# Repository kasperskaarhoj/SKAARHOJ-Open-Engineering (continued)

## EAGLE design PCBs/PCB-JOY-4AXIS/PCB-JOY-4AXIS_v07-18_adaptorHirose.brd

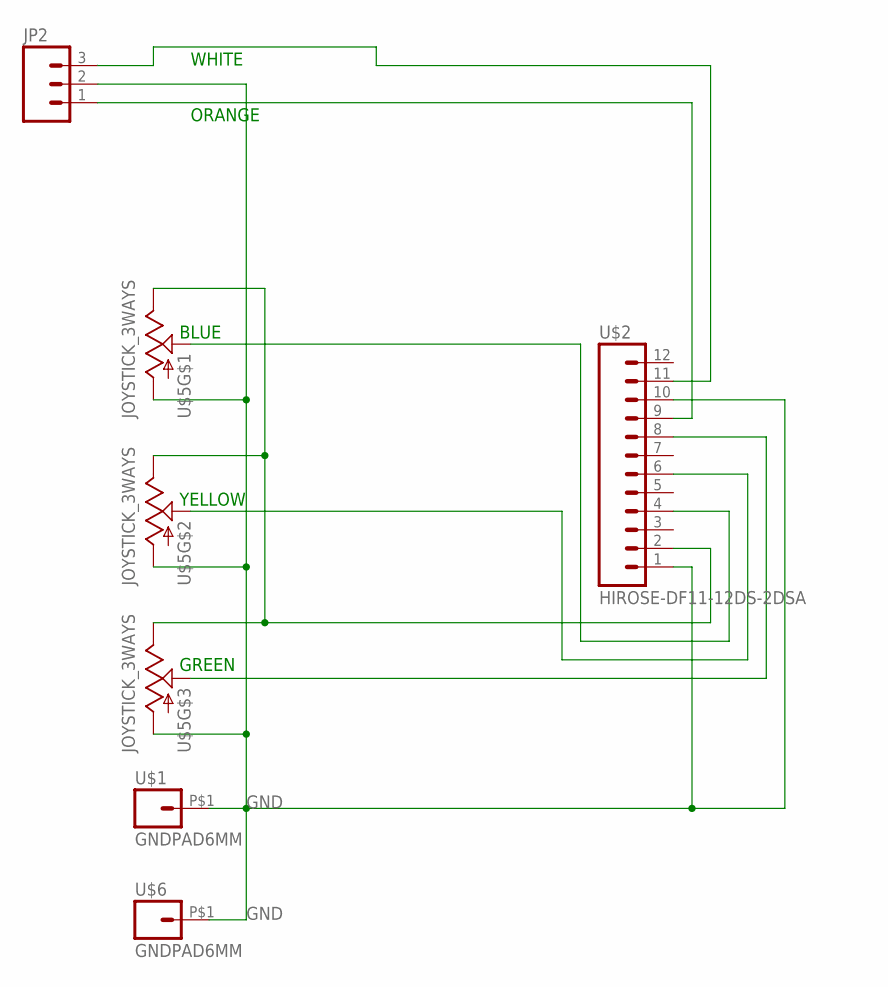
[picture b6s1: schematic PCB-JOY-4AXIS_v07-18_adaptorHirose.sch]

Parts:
JP2: M03PTH; 1X03
U$1, U$6: GNDPAD6MM; 3.2MMPAD6MM
U$2: HIROSE-DF11-12DS-2DSA; 2X6HIROSE_DF11-12DS-2DSA
U$5: JOYSTICK_3WAYS; JOYSTICK

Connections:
GND: JP2.2, U$1.P$1, U$2.1, U$2.10, U$5.LR_COM (A), U$5.ROT_COM (A), U$5.UD_COM (A), U$6.P$1
unnamed: U$2.2, U$5.LR_V (E), U$5.ROT_V (E), U$5.UD_V (E)
unnamed: U$2.4, U$5.LR_C (S)
unnamed: U$2.6, U$5.UD_C (S)
unnamed: U$2.8, U$5.ROT_C (S)
unnamed: JP2.1, U$2.9
unnamed: JP2.3, U$2.11

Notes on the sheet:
GREEN
ORANGE
WHITE
YELLOW
BLUE

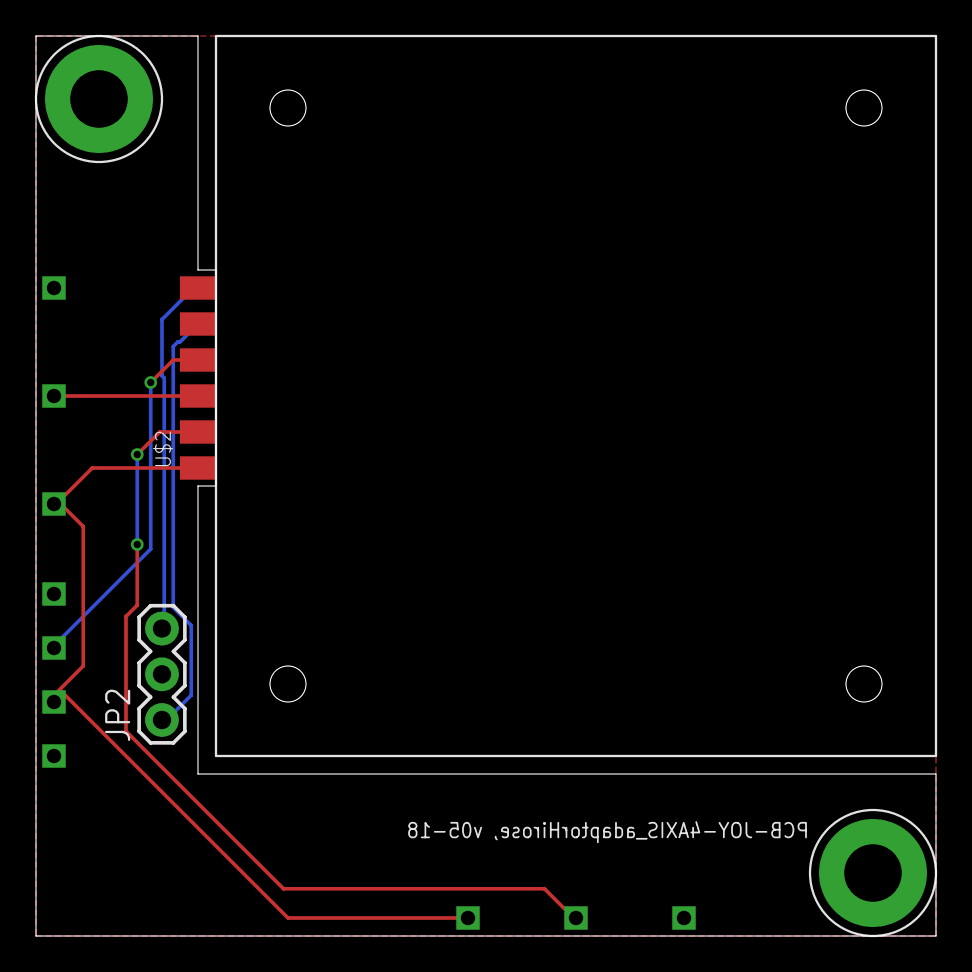
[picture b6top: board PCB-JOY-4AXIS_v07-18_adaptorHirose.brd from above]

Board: 2 copper layers, 50.0 x 50.0 mm, 5 parts (0 on the bottom side), 7 nets.

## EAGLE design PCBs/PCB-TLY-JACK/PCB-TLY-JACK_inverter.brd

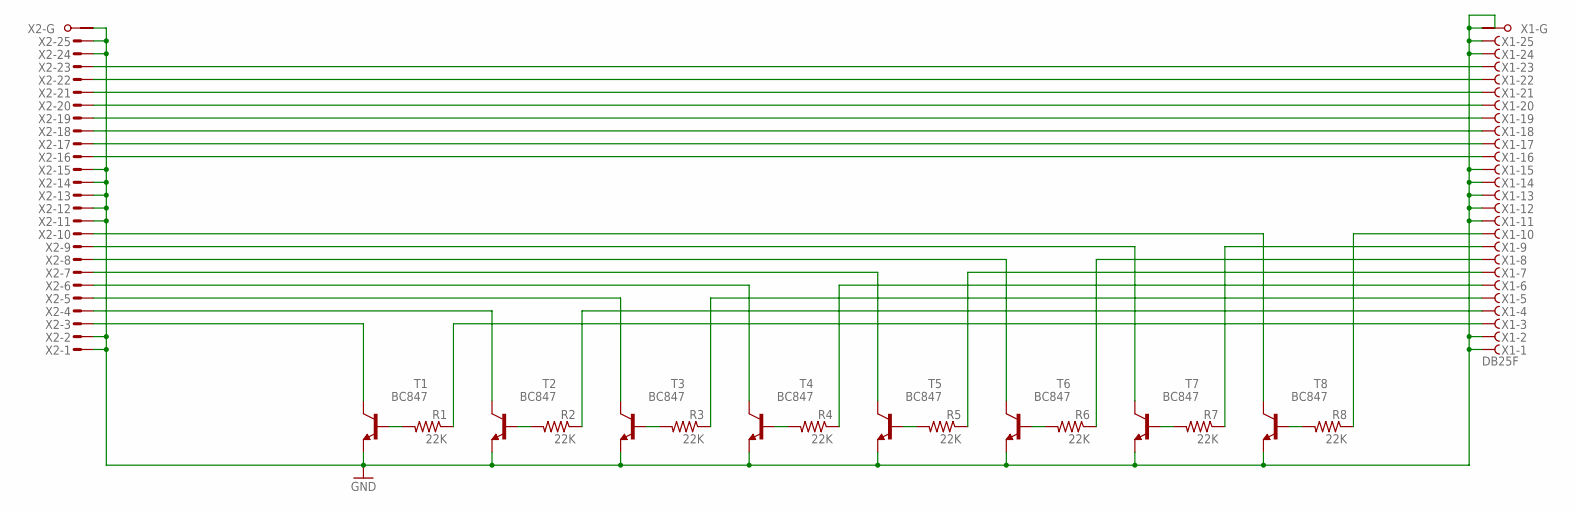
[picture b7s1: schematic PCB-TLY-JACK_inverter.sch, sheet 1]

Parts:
R1, R2, R3, R4, R5, R6, R7, R8: 22K; 0603-RES
T1, T2, T3, T4, T5, T6, T7, T8: BC847; SOT23
X1: DB25F; F25HP
X2: M25HPS; M25HP

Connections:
GND: T1.2 (E), T2.2 (E), T3.2 (E), T4.2 (E), T5.2 (E), T6.2 (E), T7.2 (E), T8.2 (E), X1.1 (F), X1.2 (F), X1.11 (F), X1.12 (F), X1.13 (F), X1.14 (F), X1.15 (F), X1.24 (F), X1.25 (F), X1.G1, X1.G2, X2.1 (M), X2.2 (M), X2.11 (M), X2.12 (M), X2.13 (M), X2.14 (M), X2.15 (M), X2.24 (M), X2.25 (M), X2.G1
unnamed: X1.23 (F), X2.23 (M)
unnamed: T8.3 (C), X2.10 (M)
unnamed: R1.2, T1.1 (B)
unnamed: T7.3 (C), X2.9 (M)
unnamed: X1.22 (F), X2.22 (M)
unnamed: T6.3 (C), X2.8 (M)
unnamed: T5.3 (C), X2.7 (M)
unnamed: T4.3 (C), X2.6 (M)
unnamed: X1.21 (F), X2.21 (M)
unnamed: T3.3 (C), X2.5 (M)
unnamed: T2.3 (C), X2.4 (M)
unnamed: R2.2, T2.1 (B)
unnamed: X1.20 (F), X2.20 (M)
unnamed: R3.2, T3.1 (B)
unnamed: R4.2, T4.1 (B)
unnamed: R5.2, T5.1 (B)
unnamed: X1.19 (F), X2.19 (M)
unnamed: R6.2, T6.1 (B)
unnamed: R7.2, T7.1 (B)
unnamed: R8.2, T8.1 (B)
unnamed: X1.18 (F), X2.18 (M)
unnamed: T1.3 (C), X2.3 (M)
unnamed: R1.1, X1.3 (F)
unnamed: X1.17 (F), X2.17 (M)
unnamed: R2.1, X1.4 (F)
unnamed: R3.1, X1.5 (F)
unnamed: R4.1, X1.6 (F)
unnamed: X1.16 (F), X2.16 (M)
unnamed: R5.1, X1.7 (F)
unnamed: R6.1, X1.8 (F)
unnamed: R7.1, X1.9 (F)
unnamed: R8.1, X1.10 (F)

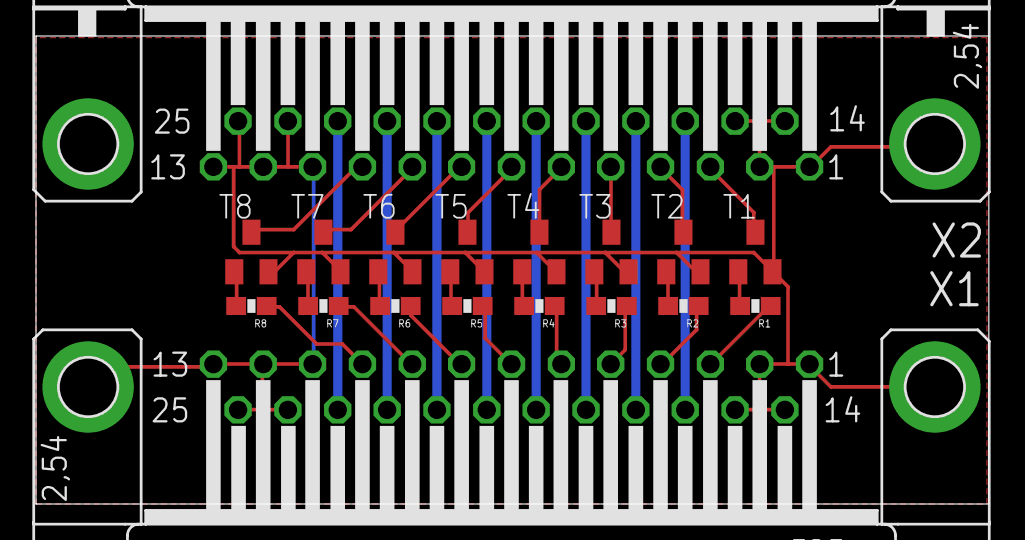
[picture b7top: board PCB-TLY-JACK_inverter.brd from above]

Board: 2 copper layers, 52.9 x 26.0 mm, 18 parts (0 on the bottom side), 33 nets.

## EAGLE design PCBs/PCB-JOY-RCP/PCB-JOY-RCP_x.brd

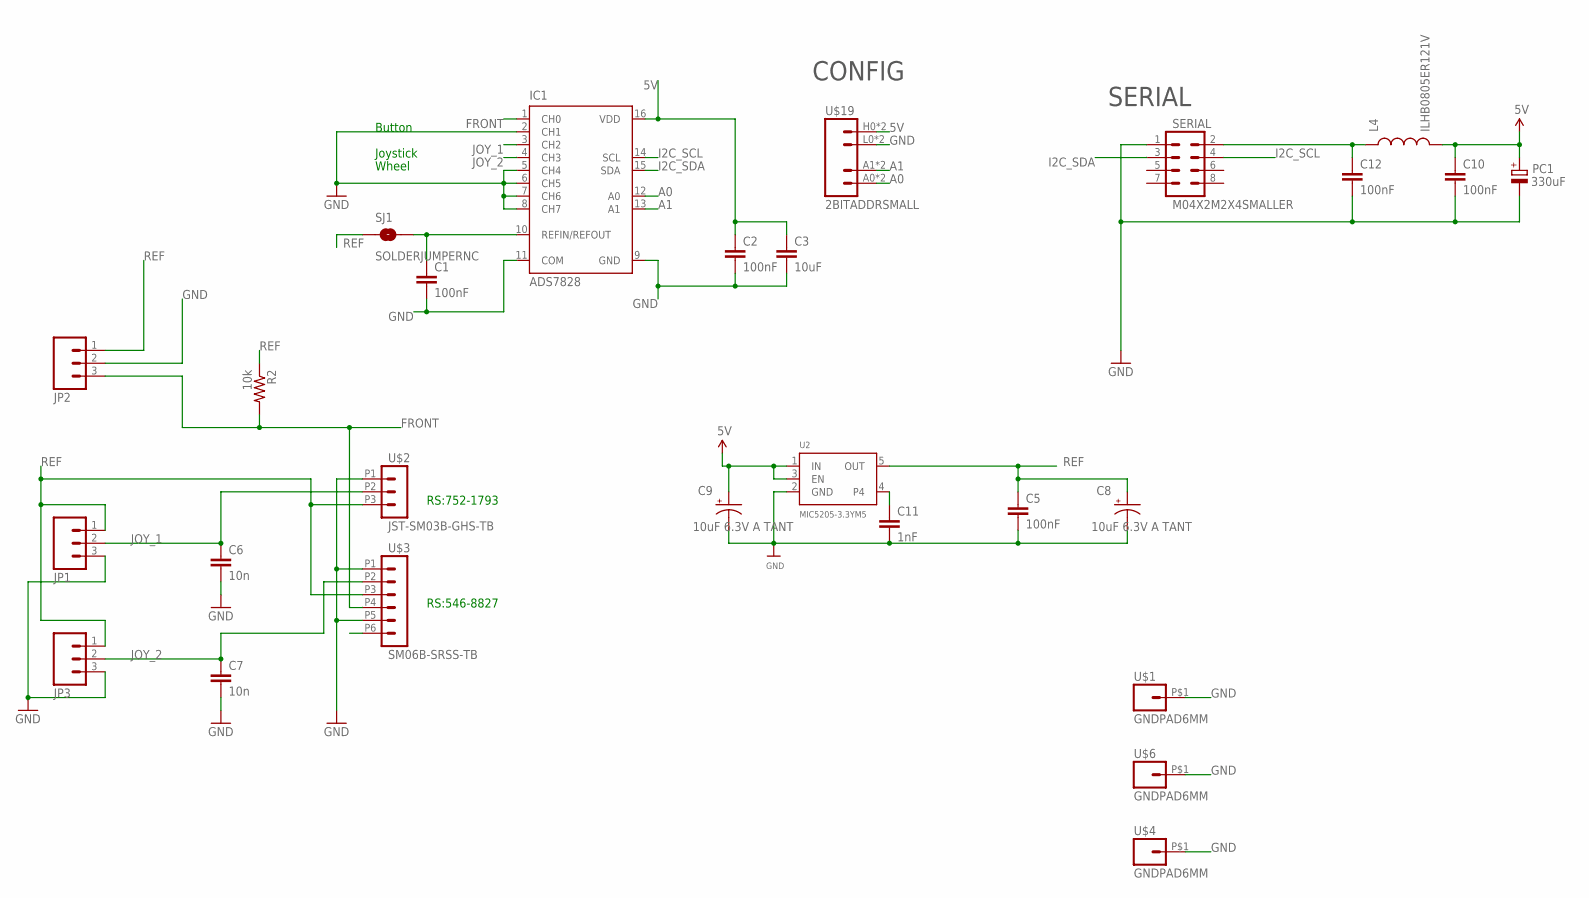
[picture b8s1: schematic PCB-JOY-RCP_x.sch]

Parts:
C1, C2, C5, C10, C12: 100nF; 0603-CAP
C3: 10uF; 0805
C6, C7: 10n; 0603-CAP
C8, C9: 10uF 6.3V A TANT; EIA3216
C11: 1nF; 0603-CAP
IC1: ADS7828; TSSOP16-PW
JP1, JP2, JP3: M03PTH; 1X03
L4: ILHB0805ER121V; 0805
PC1: 330uF; PANASONIC_D
R2: 10k; 0603-RES
SERIAL: M04X2M2X4SMALLER; M2X4SMALLER
SJ1: SOLDERJUMPERNC; SJ_2S
U2: MIC5205-3.3YM5; SOT23-5
U$1, U$4, U$6: GNDPAD6MM; 3.2MMPAD6MM
U$2: JST-SM03B-GHS-TB
U$3: SM06B-SRSS-TB; JST-SM06B-SRSS-TB
U$19: 2BITADDRSMALL; 2BITADDR_SMALL

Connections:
5V: C2.1, C3.1, C9.A (+), C10.1, IC1.16 (VDD), L4.2, PC1.+, U2.1 (IN), U2.3 (EN), U$19.H0 (VCC), U$19.H1 (VCC)
A0: IC1.12 (A0), U$19.A0 (A1), U$19.AS0 (A1)
A1: IC1.13 (A1), U$19.A1 (A2), U$19.AS1 (A2)
ARD_5V: C12.1, L4.1, SERIAL.2
FRONT: IC1.1 (CH0), JP2.3, R2.2, U$3.P4 (4)
GND: C1.2, C2.2, C3.2, C5.2, C6.2, C7.2, C8.C (-), C9.C (-), C10.2, C11.2, C12.2, IC1.2 (CH1), IC1.5 (CH4), IC1.6 (CH5), IC1.7 (CH6), IC1.8 (CH7), IC1.9 (GND), IC1.11 (COM), JP1.3, JP2.2, JP3.3, PC1.-, SERIAL.1, U2.2 (GND), U$1.P$1, U$2.P1 (1), U$3.P1 (1), U$3.P5 (5), U$4.P$1, U$6.P$1, U$19.L0 (GND), U$19.L1 (GND)
I2C_SCL: IC1.14 (SCL), SERIAL.4
I2C_SDA: IC1.15 (SDA), SERIAL.3
JOY_1: C6.1, IC1.3 (CH2), JP1.2, U$2.P2 (2)
JOY_2: C7.1, IC1.4 (CH3), JP3.2, U$3.P2 (2)
unnamed: C1.1, IC1.10 (REFIN/REFOUT), SJ1.2
unnamed: C11.1, U2.4
REF: C5.1, C8.A (+), JP1.1, JP2.1, JP3.1, R2.1, SJ1.1, U2.5 (OUT), U$2.P3 (3), U$3.P3 (3)

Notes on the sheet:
CONFIG
Joystick
Wheel
Button
SERIAL
RS:546-8827
RS:752-1793

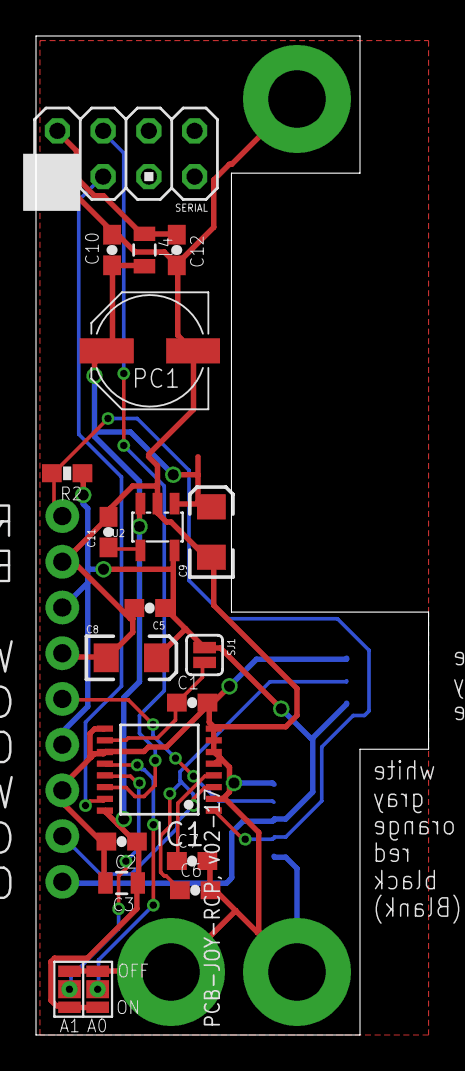
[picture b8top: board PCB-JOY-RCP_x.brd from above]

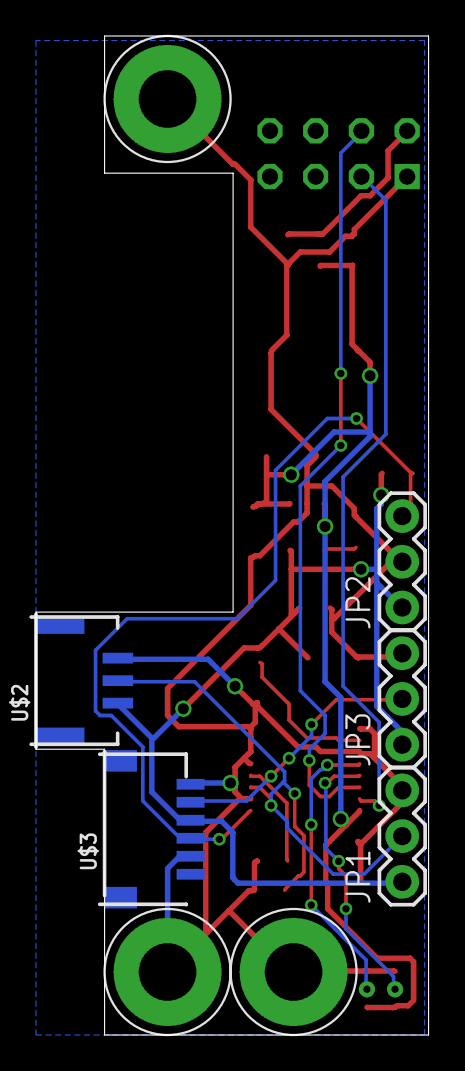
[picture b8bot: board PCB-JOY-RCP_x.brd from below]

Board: 2 copper layers, 21.8 x 55.5 mm, 27 parts (8 on the bottom side), 13 nets.

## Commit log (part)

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2016-12-20 Config updates
2016-12-20 Preset recall speed PanaAWHE
2016-12-21 Autoiris support PanaAWHE
2016-12-21 More panaawhe updates
2016-12-21 Config files updates
2017-01-03 Generalisation of system limiter handler
2017-01-03 Updates to panasonic support
2017-01-03 Created SkaarhojSIL library
2017-01-03 Updates to SkaarhojSIL
2017-01-03 Swapped green and blue in SkaarhojSIL
2017-01-04 Merge remote-tracking branch 'origin/master'
    # Conflicts:
    # ArduinoLibs.zip
2017-01-05 Update to manual
2017-01-05 Manual
2017-01-05 ArduinoLibs.zip
2017-01-05 C30_ArduinoEthernet_added
2017-01-06 SkaarhojSIL changes
2017-01-16 Small changes to analog slider readout
2017-01-16 Small updates to Aja KUMO library
2017-01-17 Aja kumo changes
2017-01-20 Fix for > 16 videhub channels
2017-01-20 Fix for endpoint detection for analog inputs with large end end offsets
2017-01-20 Initial commit of SkaarhojUDP class
2017-01-31 ASDF
2017-01-31 Added stuff
2017-02-13 Added MD5 Library
2017-02-14 Corrected an error in the function that sets normalised zoom
2017-02-16 Syntax bug
    New line had sneaked in.
2017-02-17 Updates to PanaAWHE library
2017-02-20 Cleaning up
2017-02-20 Cleanup
2017-02-20 Corrected SS pin number
2017-03-01 Updated example for Skaarhoj_E21TVSL
2017-03-27 Modifications to BI8 Library
2017-04-05 VMIx updates
2017-05-10 Aja kumo updates
2017-05-11 1x16 GPIO FIx
2017-05-24 Updated USB core source to newest version
2017-05-24 Added supersource support to ATEMuni library
2017-05-24 Added string length readout to atem library functions
2017-05-30 Corrected string bug, reverted type size bug
2017-05-30 Mapped Pins IO1/IO2
2017-06-26 Fixed contrast settings in ATEM lib, various updates
2017-06-26 Added intial clearing of displays for 32x256 OLED
2017-07-04 Various PCB updates
2017-07-05 Increased timeout in UDP messenger
2017-07-05 Indent
2017-07-05 Removed ClientBMDCamCtrl lib
2017-07-05 Increased SkaarhojBufferTools buffersize
2017-07-07 Increased number of supported cameras to 20
2017-07-07 Increased characters in labels to 20 (21) from 9 (10) Added functions for getting number of inputs and outputs
2017-07-07 See previous commit
2017-07-07 New class for BlackMagic Design Multiview, not tested yet in this commit.
2017-07-07 Manuals first commit
2017-07-09 More manuals and names changed. New info in manuals.
2017-07-10 Updated manuals with better picture quality (export to PDF via Print dialog instead)
2017-07-20 Panasonic AWHE fixes
2017-07-21 AJA Kumo library updates
2017-07-21 Small bugfix
2017-07-21 Another fix
2017-07-21 Readout of protection status for destinations
2017-07-24 Added comment about "Hold Down" for memory groups
2017-07-24 First beta version of this document
2017-07-28 Kumo labels
2017-08-03 Updated Tally System sketch
2017-08-25 Added way to read out the socket number for clients - found that useful...
2017-08-28 Added "sockets" command for serial monitor.
2017-08-28 added functions to read out socket status information. Added a call to reset the wiznet chips registers as a part of the begin() method - otherwise old sockets might still be open!
2017-08-28 Added tcp bulk transfer methods
2017-08-28 Added a function to advance the internal pointer
2017-08-28 Typo
2017-08-28 Fixed bug with WriteMR
2017-08-28 Initialisation bug
2017-08-28 Init fix
2017-08-29 BMD SDI small fix
2017-08-29 Increased init delay to original value for W5500
2017-08-30 Smartscope network fix
2017-09-01 SKAARHOJ UniSKetch TCP Client library + update to parent library
2017-09-01 Fixes
2017-09-04 ATEMbase.cpp prevent lockup if too many init packes are being sent
2017-09-04 HWC Tie-ing functions in class
2017-09-04 Fixed bugs
2017-09-04 Fixed a bug where constrain didn't properly work with parseInt() - reason seemed to be that parseInt() is passed by reference so it was called multiple times inside constrain instead of just passing 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
2017-09-04 Moved data length to correct byte position
2017-09-04 Added initialisation of ATEM CCU parameters
2017-09-05 Sockets keep alive readout
2017-09-05 Momentary override setting
2017-09-05 Added manual for non UniSketch based controllers
2017-09-05 Added RCP Manual
2017-09-06 Lots of manual updates and other documents
2017-09-11 Added getOverride method to BMDSDICameraControl
2017-09-11 aja humo upgraded to 64 sources/destinations
2017-09-20 Fixed int8 length byte location ATEM CCU
2017-09-20 BMD I2C Buffer length taken from Wire.h
2017-09-20 Changed to absolute focus
2017-09-25 Added 64x32 test graphics along with Python scripts for testing the UniSketch TCP Client
2017-09-26 Updated UniSketch TCP client a lot with graphics and other handshaking.
2017-09-26 Added support for partial writing of display content.
2017-09-26 Fixed a bug in relation to ping (where it would flood pings in certain circumstances) Also added more efficient reading from WizNet chip (filling a buffer)
2017-09-26 Updated a new Python 3 UniSketch TCP Client server-test-scripts
2017-09-26 Updated manuals
2017-09-27 updated, smaller size
2017-09-28 Test
2017-10-02 Updates (goes along with Shogun updates)
2017-10-02 Shogun documentation
2017-10-03 mode debug output in case of buffer overflow.
2017-10-05 KUMO changed to hex indexing for inputs
2017-10-05 DHCP Client name
2017-10-06 Changed DHCP initial timeout to 10 s
2017-10-06 New chip added AS5045B
2017-10-06 Additions
2017-10-08 EthernetClient bugs
2017-10-08 A couple more ethernet fixes
2017-10-08 Removed some debugging messages
2017-10-20 ATEM Library updates
2017-10-24 Joystick hasMoved bug fix
2017-10-24 Added utility/w5100.h to panasonic library for legacy support
2017-10-27 Display fixes
2017-10-31 EADOGM_Color_test
2017-12-14 Update with comment for Windows Defender Firewall
2017-12-18 Update with "Sensor Gain / Camera Gain Setting Range" in Device Configurations
2018-01-19 merge
2018-03-23 Update to propper version (had been overwritten) + update to Device Configurations | Tally Override
2018-03-26 Update w. firmware version for AJA KUMO firmware
2018-04-27 Adaptor PCB start for hires connector
2018-04-27 4AXISHirose
2018-05-22 Examples
2018-06-01 Added "Flag Condition" action to manual
2018-06-13 Update w. "Set Mark in/out + cancel" + "Trigger Shortcut"
2018-06-13 Added initial work on PTZ Control manual. How the "Camera Selector" work and how to set IP
2018-06-13 Various small updates
2018-06-20 Update w. Multicast Data Section
2018-06-20 Save update
2018-08-07 Small updates
2018-08-08 Updates with camera selector on camera itself for NewTek
2018-08-08 Design update to PTZ Control and Added DC_LumensNewTek for instructions on Device Core options
2018-08-08 Added section with "Triggering Actions from Binary Inputs". Relevant for AW-RP50/120 binary cases.
2018-08-29 Updated to include description of the default config “Binary AUX Routing”
2018-08-29 Added Firmware Upgrade instructions for SDI-B4 Link
2018-08-31 Update with section for Configurations with Multiple PTZ Brand
2018-10-01 aside
2018-10-01 Large update to UniSketch Manual
2018-10-02 Save adjustment
2018-10-02 Updates w. non registered controllers
2018-10-02 More updates
2018-10-05 Note for SKAARHOJ controllers with Blackmagic 3G-SDI Arduino Shields and Studio Fiber Converter/Camera Fiber Converter
2018-10-05 SKAARHOJ_RCP_Manual_November_2016_V2
2018-10-08 Updates w. "Setting IP for non UniSketch Based Controllers"
2018-10-08 Updates w. "Connection between RCP and ETH-SDI Link using ETH2SDI Firmware"
2018-10-08 Updates and new Device Core Manual
2018-10-18 Moved "Triggering Actions from Binary Inputs" from DC_System to UniSketch Manual
2018-10-19 Updates Sensor Gain / Camera Gain Setting Range (have been deprecated by October 2018)
2018-10-19 Roll back
2018-10-30 Update w. Sensor Gain / Camera Gain Setting Range example
2018-10-30 Updates with further details in example on how to access the config page.
2018-10-30 Added manual with actions necessary for BrightEye NXT <-> SKAARHOJ connection.
2018-10-31 Added manual with actions necessary for Dream Chip ATOM one Mini <-> SKAARHOJ connection.
2018-11-02 Remove DLink DGS-1100-08P as recommended network switch after further investigation discovering poor performance.
2018-11-02 Update with advices against the DGS-1100-08P from D-Link.
2018-11-05 Updates to Generic VISCA to include serial communication via RS422 and RS232. Updates to Lumens/NewTek with Device Core option to set communication via serial.
2018-11-05 Save updates
2018-11-07 Update with iris (f-stop)
2018-11-07 Updates w. CCU Settings
2018-11-12 Updates with firmware version for NewTek
2018-11-12 Updated with firmware version of NewTek camera
2018-11-17 c++ library for using raw panels
2018-11-17 PCBs
2018-11-19 Macro Files
2018-11-19 Updates and ARRI Amira
2018-11-22 Updates with section "The Controller Appears Bricked/Non Responsive "
2018-11-22 Added manual for AJA FS4 + various updates
2018-11-22 Small updates + save update
2018-11-27 Updating PTZ Manual with details about PTZ Speed and more. Adding Vaddio RobotSHOT manual
2018-11-29 Updates to manual with new vMix Bridge and updates to UniSketch OS
2018-11-29 Updates with more actions
2018-12-03 Updated actions
2018-12-15 encsolo
2018-12-15 mreplay labels
2018-12-16 no message
2018-12-17 Updates with "Static IP Address or DHCP"
2019-01-08 Additional graphics
2019-01-17 Added introduction/manual for ETH-LANC Link
2019-01-18 Updated with some examples for Raw Panel mode Python scripts. Updated Raw Panel documentation (UniSketch TCP Client) and converted the source to ODT instead of Pages.
2019-01-30 Updates with graphics and section with confirmation of connection
2019-01-30 Graphics updates
2019-01-31 Added manual for Panasonic AW-RP120
2019-02-12 Beginning of new manual and Device Core
2019-02-12 Some network updates
2019-02-12 Note about remembering to activate the TCP Server Device Core
2019-02-14 OSC (Open Sound Control)
2019-02-14 Update to naming
2019-03-07 Added Panasonic RS422 manual
2019-03-07 Save udates
2019-04-26 Updates from Alpha to working state
2019-05-01 Updates filenaming
2019-05-01 Update with pinout for DB9 connector on RCP
2019-05-02 Updates with video from Dream Chip
2019-05-03 New Manual
2019-05-03 Smaller version
2019-05-03 Updates to pinout tally box
2019-05-05 Hi Res joystick stykliste
2019-05-08 Updated Raw Panel manual with Topology command + a script with reference implementation of topology
2019-05-19 Raw Panel - topology stuff and changes to manual - in progress.
2019-05-19 TCPserver.py test script used for TCPClient device core
2019-05-19 Manual for TCP Client device core.
2019-05-20 Save updates + Firmware notice on Agile camera
2019-05-29 Save updates + new manual
2019-06-06 Fixed error related to setting device core options.
2019-06-12 Initial work on 2 new Device Core manuals
2019-06-19 Updates with Port Selection Windows
2019-06-20 Small updates with connection examples
2019-06-24 Various updates
2019-07-04 Work on new manuals and various updates
2019-07-04 More work
2019-07-04 Initial testing shows improved connectivity handling with v8.01 instead of v8.0 on the ATEM Constellation
2019-07-05 Various updates - closing in on Release
2019-08-08 Small updates with Tally
2019-08-16 New manual - work in progress
2019-08-19 Rename + updates
2019-08-20 Save updates and work in progress on HyperDeck manual
2019-08-20 Save updates to the recent additions. Work in progress
2019-08-22 Updates with DC port option
2019-08-26 Updates after Simon magic
2019-08-28 New Bolin Manual
2019-08-28 Updates after release to v2.2.151
2019-08-28 Support for AW-UE150
2019-08-28 Bolin updates
2019-08-28 Iris notification update
2019-09-02 Fixed bug
2019-09-02 Updated manual
2019-09-02 UPdate?
2019-09-02 Updated info about "\f2" and "\f3" label formatting
2019-09-02 Updated backslash to $
2019-09-03 Updates and new manual
2019-09-08 Manual updates
2019-09-08 Updated manual and added a basic script for playing with displya caching.
2019-09-09 Updates for supported cameras
2019-10-01 Some updates
2019-10-02 Updates with some branch features
2019-10-11 Updates with port selection
2019-10-22 Moving files to Github/SKAARHOJ/Support
2019-10-25 Files are moved to Support/Files/UniSketchTCPClient
